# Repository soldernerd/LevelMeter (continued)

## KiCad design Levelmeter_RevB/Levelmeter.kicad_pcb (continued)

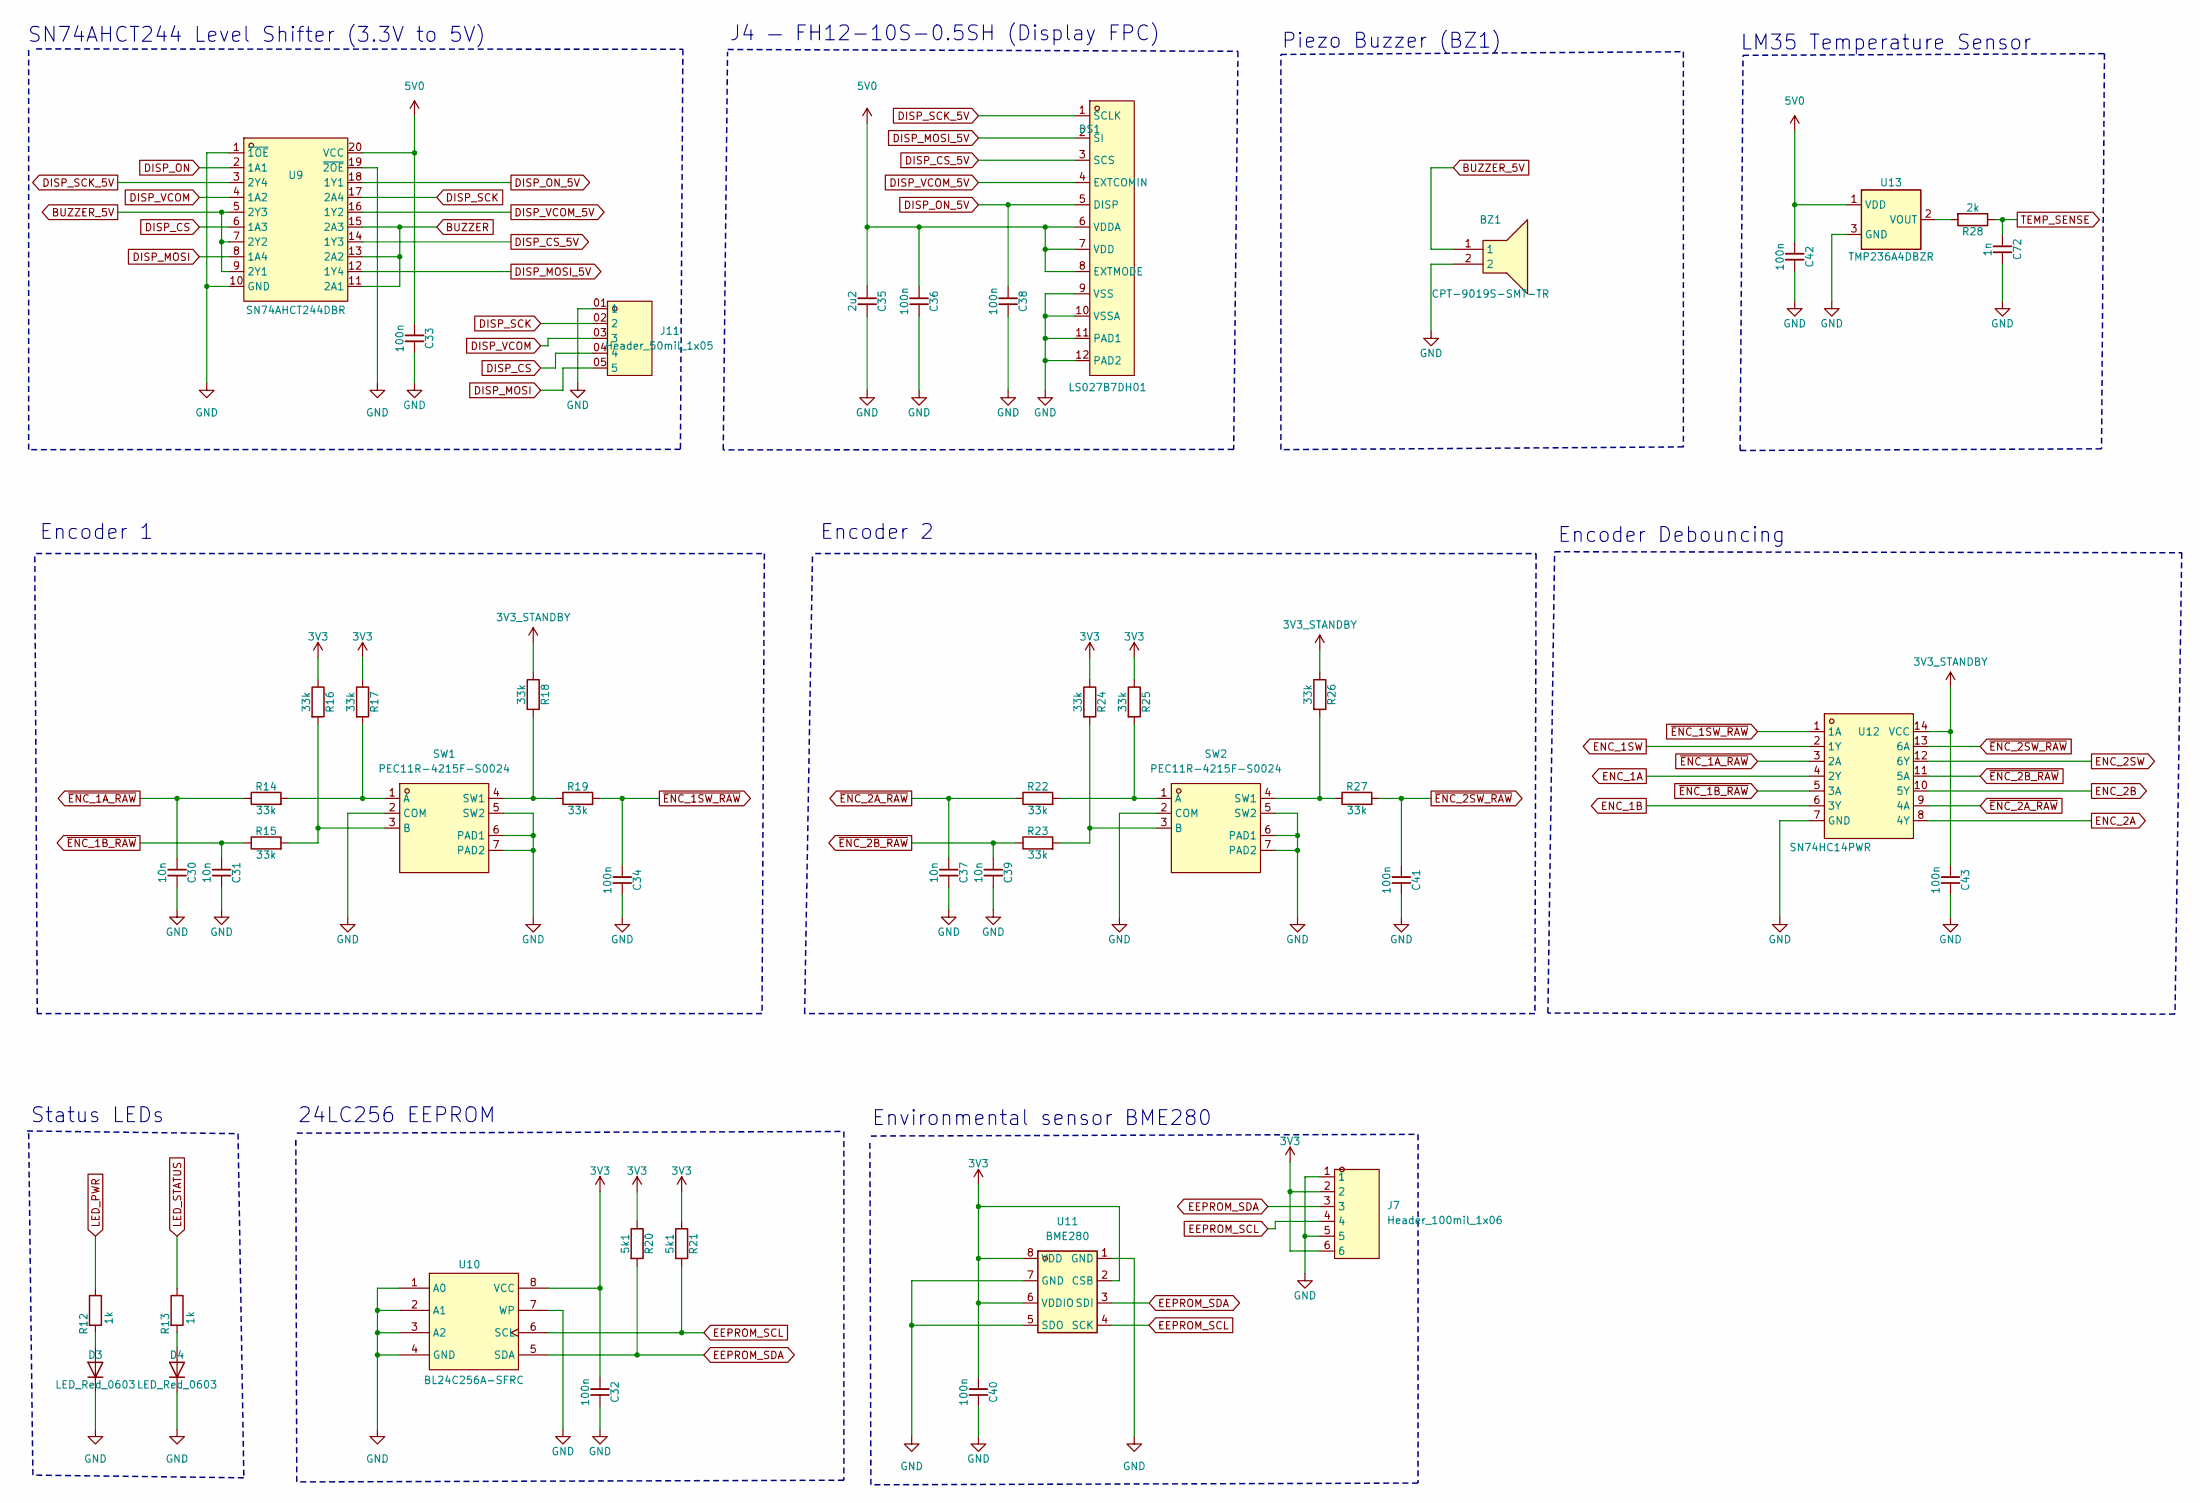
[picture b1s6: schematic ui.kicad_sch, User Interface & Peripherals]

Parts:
BZ1: CPT-9019S-SMT-TR; CPT-9019S; MPN CPT-9019S-SMT-TR; LCSC C95163
C30, C31, C37, C39: 10n; C_0603; Voltage 50V; MPN 0603B103K500NT; LCSC C57112
C32, C33, C34, C36, C38, C40, C41, C42, C43: 100n; C_0603; Voltage 50V; MPN CC0603KRX7R9BB104; LCSC C14663
C35: 2u2; C_0805; Voltage 50V; MPN CL21A225KBQNNNE; LCSC C377773
C72: 1n; C_0603; Voltage 50V; MPN CL10B102KB8NNNC; LCSC C1588
D3, D4: LED_Red_0603; LED_0603; MPN KT-0603R; LCSC C2286
DS1: LS027B7DH01; Display_LS027B7DH01; MPN LS027B7DH01; LCSC Display: C17492463, Connector: C262557
J7: Header_100mil_1x06; MPN A2541WV-6P; LCSC C225481
J11: Header_50mil_1x05
R12, R13: 1k; R_0603; MPN 0603WAF1001T5E; LCSC C21190
R14, R15, R16, R17, R18, R19, R22, R23, R24, R25, R26, R27: 33k; R_0603; MPN 0603WAF3302T5E; LCSC C4216
R20, R21: 5k1; R_0603; MPN 0603WAF5101T5E; LCSC C23186
R28: 2k; R_0603; MPN 0603WAF2001T5E; LCSC C22975
SW1, SW2: PEC11R-4215F-S0024; RotaryEncoder_PEC11R; MPN PEC11R-4215F-S0024; LCSC C143790
U9: SN74AHCT244DBR; SSOP-20; MPN SN74AHCT244DBR; LCSC C2868870
U10: BL24C256A-SFRC; TSSOP-8; MPN BL24C256A-SFRC; LCSC C110276
U11: BME280; LGA-8_2.5x2.5mm_P0.65mm; MPN BME280; LCSC C92489
U12: SN74HC14PWR; TSSOP-14; MPN SN74HC14PWR; LCSC C6821
U13: TMP236A4DBZR; SOT-23-3; MPN TMP236A4DBZR; LCSC C2872164

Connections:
3V3: C32.1, C40.1, J7.2, J7.6, R16.1, R17.1, R20.1, R21.1, R24.1, R25.1, U10.8 (VCC), U11.2 (CSB), U11.6 (VDDIO), U11.8 (VDD); also elsewhere on the board
3V3_STANDBY: C43.1, R18.1, R26.1, U12.14 (VCC); also elsewhere on the board
5V0: C33.1, C35.1, C36.1, C42.1, DS1.6 (VDDA), DS1.7 (VDD), DS1.8 (EXTMODE), U9.20 (VCC), U13.1 (VDD); also elsewhere on the board
BUZZER: U9.11 (2A1), U9.13 (2A2), U9.15 (2A3); also elsewhere on the board
BUZZER_5V: BZ1.1, U9.5 (2Y3), U9.7 (2Y2), U9.9 (2Y1)
DISP_CS: J11.04 (4), U9.6 (1A3); also elsewhere on the board
DISP_CS_5V: DS1.3 (SCS), U9.14 (1Y3)
DISP_MOSI: J11.05 (5), U9.8 (1A4); also elsewhere on the board
DISP_MOSI_5V: DS1.2 (SI), U9.12 (1Y4)
DISP_ON: U9.2 (1A1); also elsewhere on the board
DISP_ON_5V: C38.1, DS1.5 (DISP), U9.18 (1Y1)
DISP_SCK: J11.02 (2), U9.17 (2A4); also elsewhere on the board
DISP_SCK_5V: DS1.1 (SCLK), U9.3 (2Y4)
DISP_VCOM: J11.03 (3), U9.4 (1A2); also elsewhere on the board
DISP_VCOM_5V: DS1.4 (EXTCOMIN), U9.16 (1Y2)
EEPROM_SCL: J7.4, R21.2, U10.6 (SCL), U11.4 (SCK); also elsewhere on the board
EEPROM_SDA: J7.3, R20.2, U10.5 (SDA), U11.3 (SDI); also elsewhere on the board
ENC_1A: U12.4 (2Y); also elsewhere on the board
ENC_1B: U12.6 (3Y); also elsewhere on the board
ENC_1SW: U12.2 (1Y); also elsewhere on the board
ENC_2A: U12.8 (4Y); also elsewhere on the board
ENC_2B: U12.10 (5Y); also elsewhere on the board
ENC_2SW: U12.12 (6Y); also elsewhere on the board
GND: BZ1.2, C30.2, C31.2, C32.2, C33.2, C34.2, C35.2, C36.2, C37.2, C38.2, C39.2, C40.2, C41.2, C42.2, C43.2, C72.2, D3.1 (K), D4.1 (K), DS1.9 (VSS), DS1.10 (VSSA), DS1.11 (PAD1), DS1.12 (PAD2), J7.1, J7.5, J11.01 (1), SW1.2 (COM), SW1.5 (SW2), SW1.6 (PAD1), SW1.7 (PAD2), SW2.2 (COM), SW2.5 (SW2), SW2.6 (PAD1), SW2.7 (PAD2), U9.1 (~1OE), U9.10 (GND), U9.19 (~2OE), U10.1 (A0), U10.2 (A1), U10.3 (A2), U10.4 (GND), U10.7 (WP), U11.1 (GND), U11.5 (SDO), U11.7 (GND), U12.7 (GND), U13.3 (GND); also elsewhere on the board
LED_PWR: R12.1; also elsewhere on the board
LED_STATUS: R13.1; also elsewhere on the board
unnamed: D3.2 (A), R12.2
unnamed: D4.2 (A), R13.2
unnamed: R14.2, R17.2, SW1.1 (A)
unnamed: R15.2, R16.2, SW1.3 (B)
unnamed: R18.2, R19.1, SW1.4 (SW1)
unnamed: R22.2, R25.2, SW2.1 (A)
unnamed: R23.2, R24.2, SW2.3 (B)
unnamed: R26.2, R27.1, SW2.4 (SW1)
unnamed: R28.2, U13.2 (VOUT)
TEMP_SENSE: C72.1, R28.1; also elsewhere on the board
~ENC_1A_RAW: C30.1, R14.1, U12.3 (2A)
~ENC_1B_RAW: C31.1, R15.1, U12.5 (3A)
~ENC_1SW_RAW: C34.1, R19.2, U12.1 (1A)
~ENC_2A_RAW: C37.1, R22.1, U12.9 (4A)
~ENC_2B_RAW: C39.1, R23.1, U12.11 (5A)
~ENC_2SW_RAW: C41.1, R27.2, U12.13 (6A)

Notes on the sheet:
Encoder 2
Encoder Debouncing
Status LEDs
LM35 Temperature Sensor
SN74AHCT244 Level Shifter (3.3V to 5V)
Environmental sensor BME280
24LC256 EEPROM
J4 — FH12-10S-0.5SH (Display FPC)
Piezo Buzzer (BZ1)
Encoder 1

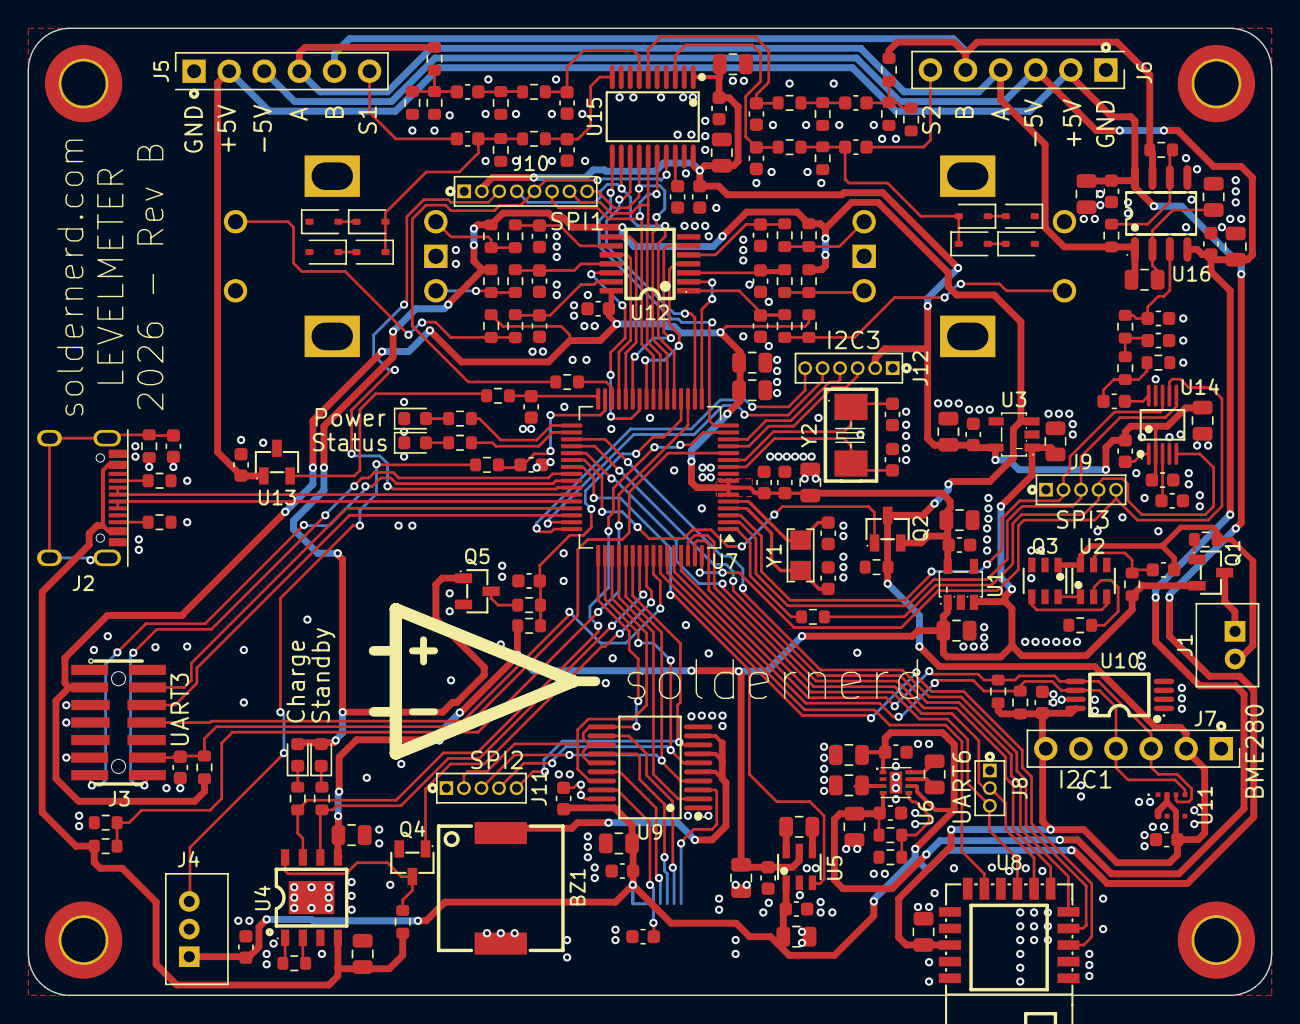
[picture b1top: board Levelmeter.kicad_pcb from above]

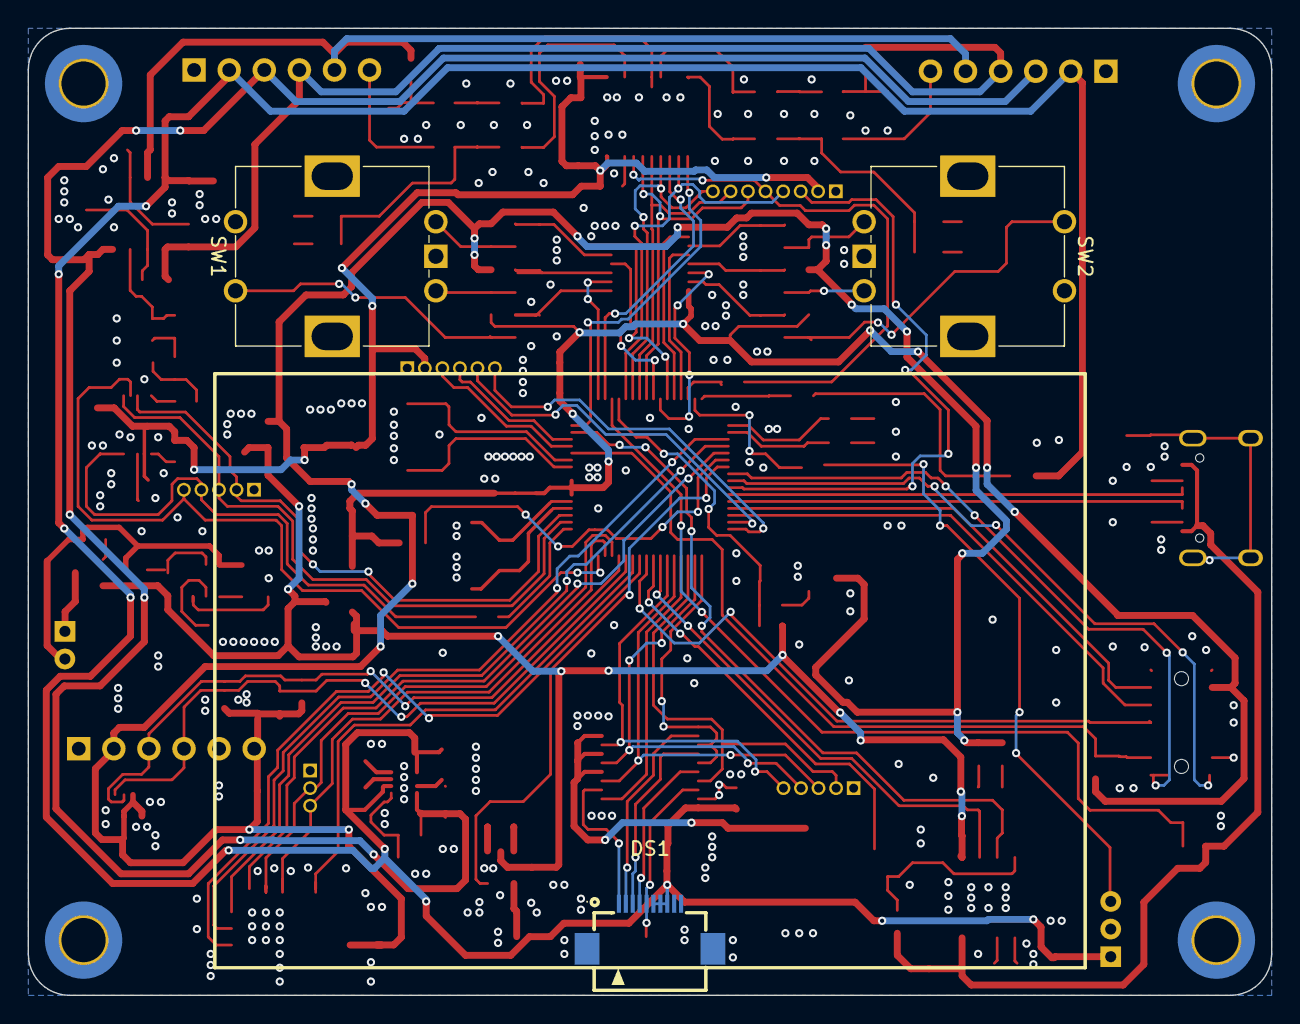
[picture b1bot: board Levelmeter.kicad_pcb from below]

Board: 4 copper layers, 90.0 x 70.0 mm, 188 parts (3 on the bottom side), 140 nets.

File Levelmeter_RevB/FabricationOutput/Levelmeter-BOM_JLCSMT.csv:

Comment,Designator,Footprint,JLCPCB Part #（optional）
CPT-9019S-SMT-TR,BZ1,CPT-9019S,C95163
1u,"C1,C4,C15,C22,C63,C64",C_0805,C28323
100n,"C2,C5,C6,C10,C12,C18,C19,C21,C23,C24,C32,C33,C34,C36,C38,C40,C41,C42,C43,C44,C45,C46,C48,C50,C51,C52,C53,C54,C59,C62,C65,C67,C68",C_0603,C14663
10u,"C3,C7,C8,C9,C11,C13,C16,C17,C20,C29,C47,C69,C70,C73,C74",C_0805,C440198
2u2,"C14,C35",C_0805,C377773
15p,"C25,C26",C_0603,C1644
33p,"C27,C28",C_0603,C1663
10n,"C30,C31,C37,C39,C49,C55,C56,C57,C58",C_0603,C57112
1n,"C60,C71,C72",C_0603,C1588
100p,C61,C_0603,C14858
220n,C66,C_0603,C21120
LED_Red_0603,"D1,D2,D3,D4",LED_0603,C2286
1N4148WS,"D5,D6,D7,D8,D9,D10,D11,D12",SOD-323,C2128
LS027B7DH01,DS1,Display_LS027B7DH01,C262557
USB_C,J2,USB_C,C165948
Header_50mil_2x07,J3,Header_50mil_2x07,C5563894
AO3401A,"Q1,Q2",SOT-23-3,C15127
FS8205A,Q3,SOT-23-6,C2830320
AO3400A,"Q4,Q5",SOT-23-3,C20917
100k,"R1,R10,R30,R33,R57",R_0603,C25803
1k,"R2,R6,R7,R12,R13",R_0603,C21190
470R,R3,R_0603,C23179
2k,"R4,R28,R35",R_0603,C22975
33k,"R5,R11,R14,R15,R16,R17,R18,R19,R22,R23,R24,R25,R26,R27,R34",R_0603,C4216
180k,R8,R_0603,C22827
68k,"R9,R32,R52",R_0603,C23231
5k1,"R20,R21,R29,R31",R_0603,C23186
10k,"R36,R37,R38,R39,R40,R41,R42,R43,R44,R45,R50,R55,R56",R_0603,C25804
680k,"R46,R47,R48,R49",R_0603,C25822
6k8,R51,R_0603,C23212
100k,R53,R_0805,C149504
10k,R54,R_0805,C17414
22R,"R58,R59",R_0603,C23345
PEC11R-4215F-S0024,"SW1,SW2",RotaryEncoder_PEC11R,C143790
LP5907MFX-3.3/NOPB,"U1,U3",SOT-23-5,C80670
DW01A,U2,SOT-23-6,C351410
TP4056,U4,ESOP-8,C382139
HX4002-MFC,U5,SOT-23-6,C172354
LM27761DSGR,U6,WSON-8-2x2-EP,C129351
STM32G0B1RET6,U7,LQFP-64,C2829307
RN4871-I/RM128,U8,RN4871,C633941
SN74AHCT244DBR,U9,SSOP-20,C2868870
BL24C256A-SFRC,U10,TSSOP-8,C110276
BME280,U11,LGA-8_2.5x2.5mm_P0.65mm,C92489
SN74HC14PWR,U12,TSSOP-14,C6821
TMP236A4DBZR,U13,SOT-23-3,C2872164
AD9833BRMZ-REEL7,U14,MSOP-10,C9652
ADS131M04IPWR,U15,TSSOP-20,C2862562
AD826,U16,SOIC-8,C114171
Q13FC1350000400,Y1,CRYSTAL-3215,C32346
X50328MSB2GI,Y2,CRYSTAL-3225,C115962

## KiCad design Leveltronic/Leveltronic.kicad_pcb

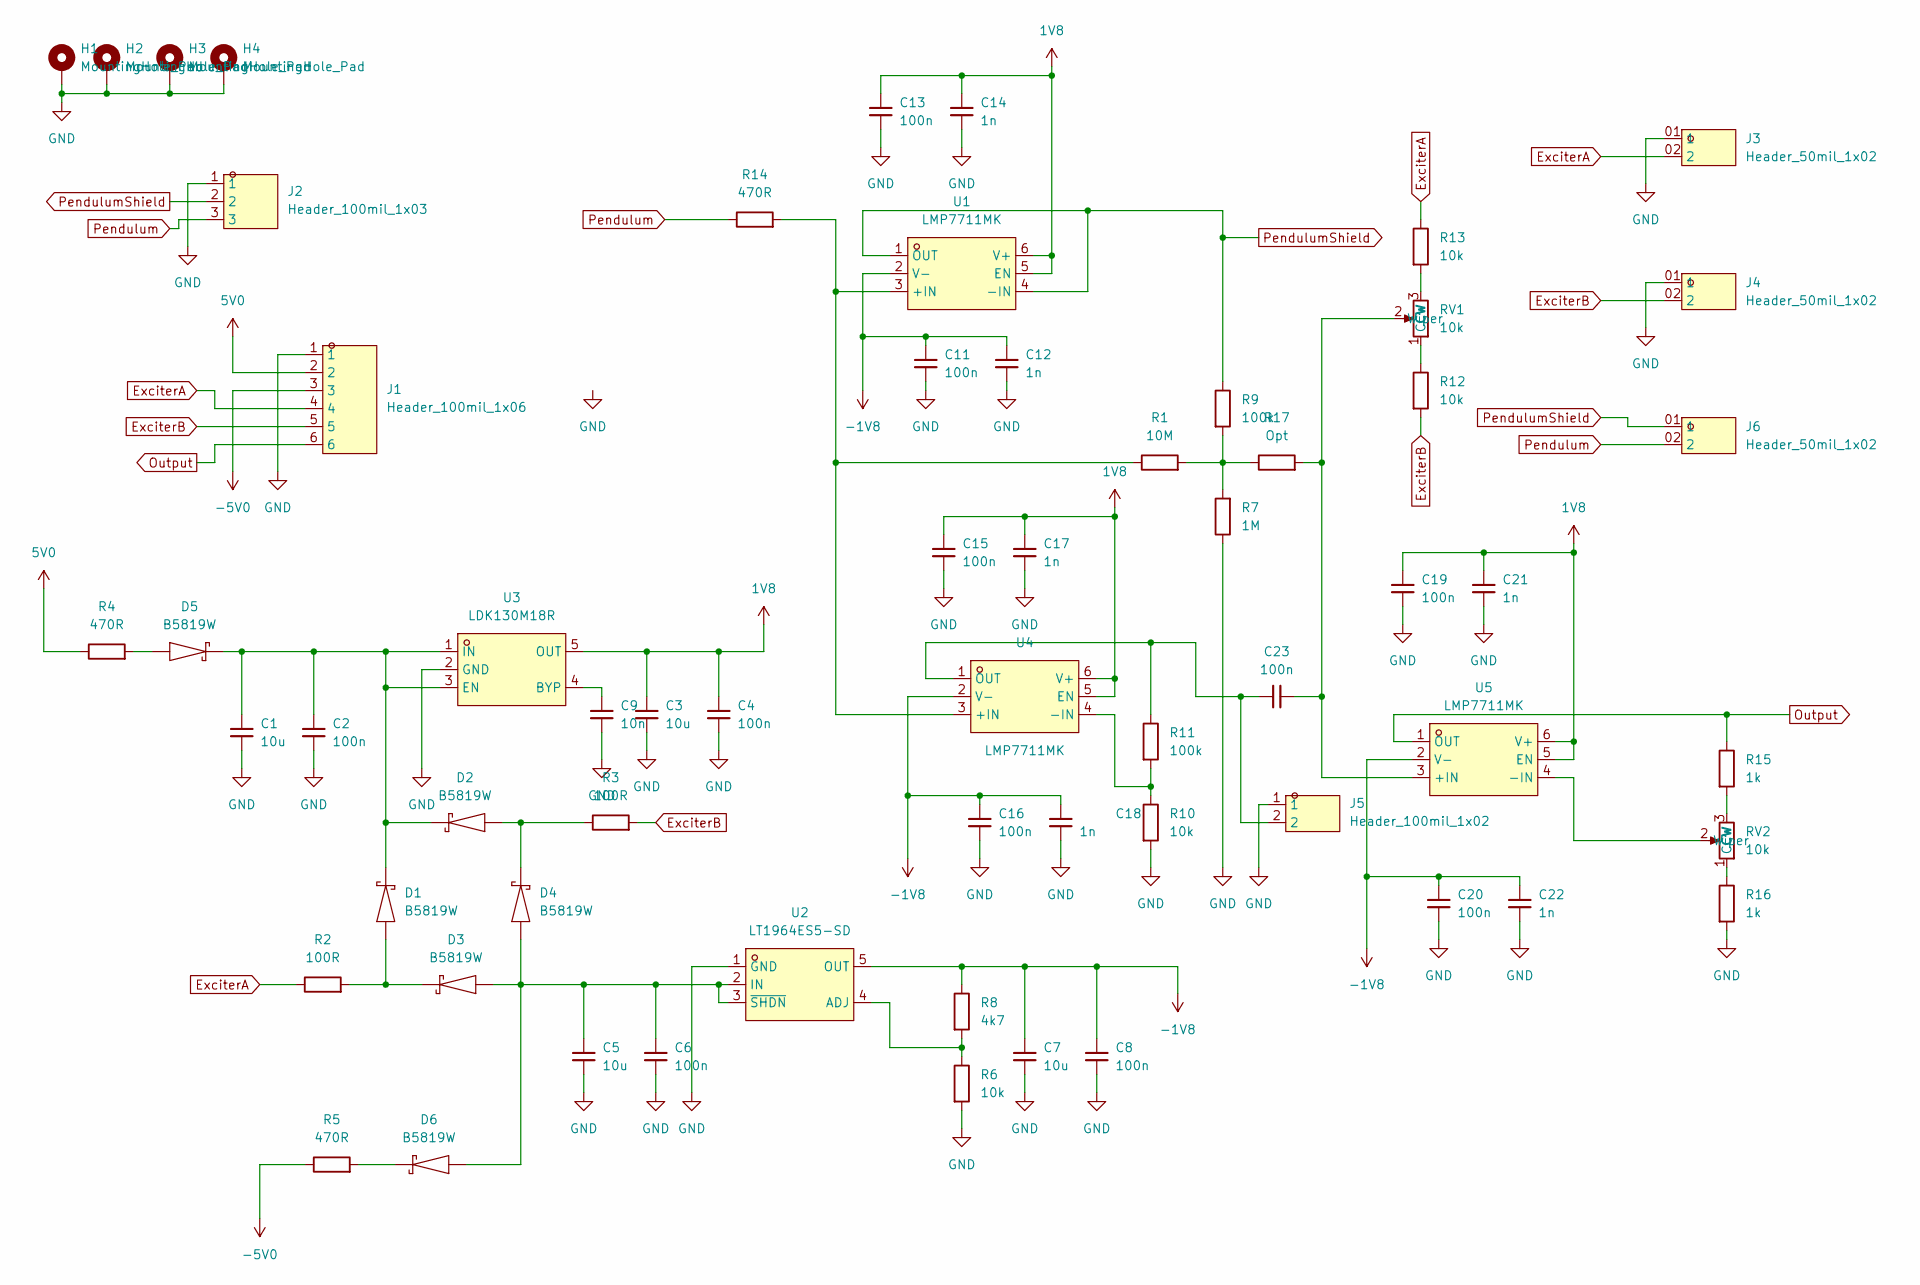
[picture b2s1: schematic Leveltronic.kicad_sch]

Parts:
C1, C3, C5, C7: 10u; C_1206; Voltage 25V; MPN GRM31CR71E106KA12L; LCSC C77093
C2, C4, C6, C8, C11, C13, C15, C16, C19, C20, C23: 100n; C_0805; Voltage 50V; MPN CC0805KRX7R9BB104; LCSC C49678
C9: 10n; C_0805; Voltage 50V; MPN CC0805KRX7R9BB103; LCSC C83170
C12, C14, C17, C18, C21, C22: 1n; C_0805; Voltage 50V; MPN CC0805KRX7R9BB102; LCSC C94121
D1, D2, D3, D4, D5, D6: B5819W; SOD-123; MPN B5819W; LCSC C8598
H1, H2, H3, H4: MountingHole_Pad; MountingHole_3.2mm
J1: Header_100mil_1x06; MPN A2541WV-6P; LCSC C225481
J2: Header_100mil_1x03; MPN A2541WV-3P; LCSC C225478
J3, J4: Header_50mil_1x02; MPN A2541WV-2P; LCSC C225477
J5: Header_100mil_1x02; MPN A2541WV-2P; LCSC C225477
J6: Header_50mil_1x02
R1: 10M; R_0805; MPN 0805W8F1005T5E; LCSC C325772
R2, R3: 100R; R_0805; MPN 0805W8F1000T5E; LCSC C17408
R4, R5, R14: 470R; R_0805; MPN 0805W8F4700T5E; LCSC C17710
R6, R10, R12, R13: 10k; R_0805; MPN 0805W8F1002T5E; LCSC C17414
R7: 1M; R_0805; MPN 0805W8F1004T5E; LCSC C17514
R8: 4k7; R_0805; MPN 0805W8F4701T5E; LCSC C17673
R9, R11: 100k; R_0805; MPN 0805W8F1003T5E; LCSC C149504
R15, R16: 1k; R_0805; MPN 0805W8F1001T5E; LCSC C17513
R17: Opt; R_0805; MPN 0805W8F1005T5E; LCSC C325772
RV1, RV2: 10k; Bourns_3296X; MPN 3296X
U1, U4, U5: LMP7711MK; SOT-23-6-LMP7711; MPN LMP7711MK/NOPB; LCSC C2057415
U2: LT1964ES5-SD; SOT-23-5; MPN LT1964ES5-SD#TRPBF; LCSC C461512
U3: LDK130M18R; SOT-23-5; MPN LDK130M18R; LCSC C377955

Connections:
1V8: C3.1, C4.1, C13.1, C14.1, C15.1, C17.1, C19.1, C21.1, U1.5 (EN), U1.6 (V+), U3.5 (OUT), U4.5 (EN), U4.6 (V+), U5.5 (EN), U5.6 (V+)
5V0: J1.2, R4.1
-1V8: C7.1, C8.1, C11.1, C12.1, C16.1, C18.1, C20.1, C22.1, R8.1, U1.2 (V-), U2.5 (OUT), U4.2 (V-), U5.2 (V-)
-5V0: J1.3, R5.1
ExciterA: J1.4, J3.02 (2), R2.1, R13.1
ExciterB: J1.5, J4.02 (2), R3.2, R12.2
GND: C1.2, C2.2, C3.2, C4.2, C5.2, C6.2, C7.2, C8.2, C9.2, C11.2, C12.2, C13.2, C14.2, C15.2, C16.2, C17.2, C18.2, C19.2, C20.2, C21.2, C22.2, H1.1 (1_1), H2.1 (1_1), H3.1 (1_1), H4.1 (1_1), J1.1, J2.1, J3.01 (1), J4.01 (1), J5.1, R6.2, R7.1, R10.2, R16.2, U2.1 (GND), U3.2 (GND)
unnamed: D1.2 (A), D3.1 (K), R2.2
unnamed: C1.1, C2.1, D1.1 (K), D2.1 (K), D5.1 (K), U3.1 (IN), U3.3 (EN)
unnamed: D2.2 (A), D4.1 (K), R3.1
unnamed: C5.1, C6.1, D3.2 (A), D4.2 (A), D6.2 (A), U2.2 (IN), U2.3 (~SHDN)
unnamed: D5.2 (A), R4.2
unnamed: D6.1 (K), R5.2
unnamed: R1.2, R7.2, R9.2, R17.1
unnamed: R12.1, RV1.1 (CCW)
unnamed: R13.2, RV1.3 (CW)
unnamed: C23.2, R17.2, RV1.2 (Wiper), U5.3 (+IN)
unnamed: R16.1, RV2.1 (CCW)
unnamed: R15.2, RV2.3 (CW)
unnamed: RV2.2 (Wiper), U5.4 (-IN)
unnamed: R1.1, R14.2, U1.3 (+IN), U4.3 (+IN)
unnamed: R6.1, R8.2, U2.4 (ADJ)
unnamed: C9.1, U3.4 (BYP)
unnamed: R10.1, R11.2, U4.4 (-IN)
unnamed: C23.1, J5.2, R11.1, U4.1 (OUT)
Output: J1.6, R15.1, U5.1 (OUT)
Pendulum: J2.3, J6.02 (2), R14.1
PendulumShield: J2.2, J6.01 (1), R9.1, U1.1 (OUT), U1.4 (-IN)

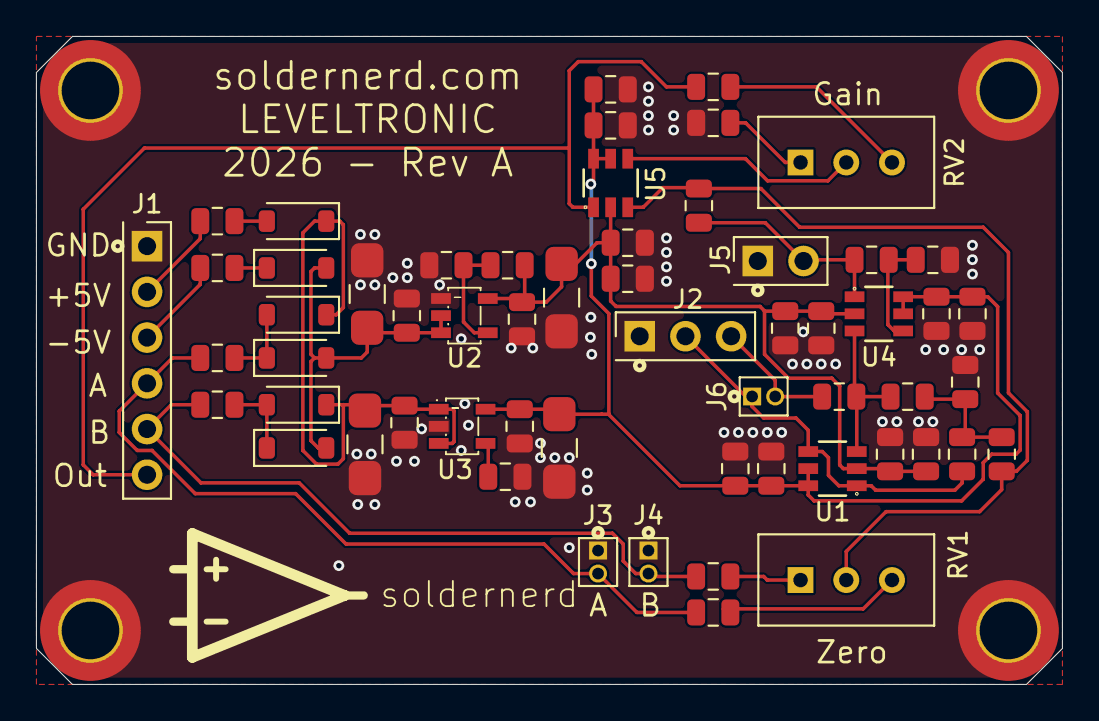
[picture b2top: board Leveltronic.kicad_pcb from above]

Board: 2 copper layers, 57.0 x 36.0 mm, 62 parts (0 on the bottom side), 28 nets.

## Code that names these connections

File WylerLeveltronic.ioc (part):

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Mcu.Name=STM32G0B1R(B-C-E)Tx
Mcu.Package=LQFP64
Mcu.UserName=STM32G0B1RETx
PA0.Mode=SYS_WakeUp0
PA0.Signal=SYS_WKUP1
PA1.Signal=GPIO_Input
PA10.Signal=GPIO_Analog
PA11\ [PA9].Signal=USB_DM
PA12\ [PA10].Signal=USB_DP
PA13.Mode=Serial_Wire
PA13.Signal=SYS_SWDIO
PA14-BOOT0.Mode=Serial_Wire
PA14-BOOT0.Signal=SYS_SWCLK
PA15.Signal=GPIO_Analog
PA2.Mode=SYS_WakeUp3
PA2.Signal=SYS_WKUP4
PA3.Signal=GPIO_Input
PA4.Signal=SPI1_NSS
PA5.Mode=Full_Duplex_Master
PA5.Signal=SPI1_SCK
PA6.Mode=Full_Duplex_Master
PA6.Signal=SPI1_MISO
PA7.Mode=Full_Duplex_Master
PA7.Signal=SPI1_MOSI
PA8.Signal=GPIO_Input
PA9.Signal=GPIO_Input
PB0.Signal=GPXTI0
PB1.Signal=GPXTI1
PB10.Signal=S_TIM2_CH3
PB11.Signal=GPIO_Output
PB12.Signal=GPIO_Output
PB15.Signal=GPIO_Input
PB2.Signal=GPXTI2
PB4.Signal=GPIO_Input
PB5.Signal=GPIO_Output
PB6.Signal=I2C1_SCL
PB7.Signal=I2C1_SDA
PB8.Signal=USART6_TX
PB9.Signal=USART6_RX
PC10.Signal=SPI3_SCK
PC11.Signal=S_TIM1_CH4
PC12.Signal=SPI3_MOSI
PC13.Signal=GPIO_Output
PC14-OSC32_IN\ (PC14).Mode=LSE-External-Oscillator
PC14-OSC32_IN\ (PC14).Signal=RCC_OSC32_IN
PC15-OSC32_OUT\ (PC15).Mode=LSE-External-Oscillator
PC15-OSC32_OUT\ (PC15).Signal=RCC_OSC32_OUT
PC3.Signal=GPIO_Output
PC4.Signal=GPXTI4
PC5.Mode=SYS_WakeUp4
PC5.Signal=SYS_WKUP5
PC6.Signal=GPIO_Output
PC7.Signal=GPIO_Output
PC8.Signal=GPIO_Analog
PC9.Signal=S_TIM3_CH4
PD0.Signal=SPI2_NSS
PD1.Mode=TX_Only_Simplex_Unidirect_Master
PD1.Signal=SPI2_SCK
PD2.Signal=GPIO_Output
PD3.Signal=GPIO_Output
PD4.Mode=TX_Only_Simplex_Unidirect_Master
PD4.Signal=SPI2_MOSI
PD5.Signal=GPIO_Input
PD6.Signal=GPIO_Output
PD8.Signal=USART3_TX
PD9.Signal=USART3_RX
PF0-OSC_IN\ (PF0).Mode=HSE-External-Oscillator
PF0-OSC_IN\ (PF0).Signal=RCC_OSC_IN
PF1-OSC_OUT\ (PF1).Mode=HSE-External-Oscillator
PF1-OSC_OUT\ (PF1).Signal=RCC_OSC_OUT
RCC.HSE_VALUE=8000000
RCC.SYSCLKFreq_VALUE=64000000
RCC.SYSCLKSource=RCC_SYSCLKSOURCE_PLLCLK
board=custom
